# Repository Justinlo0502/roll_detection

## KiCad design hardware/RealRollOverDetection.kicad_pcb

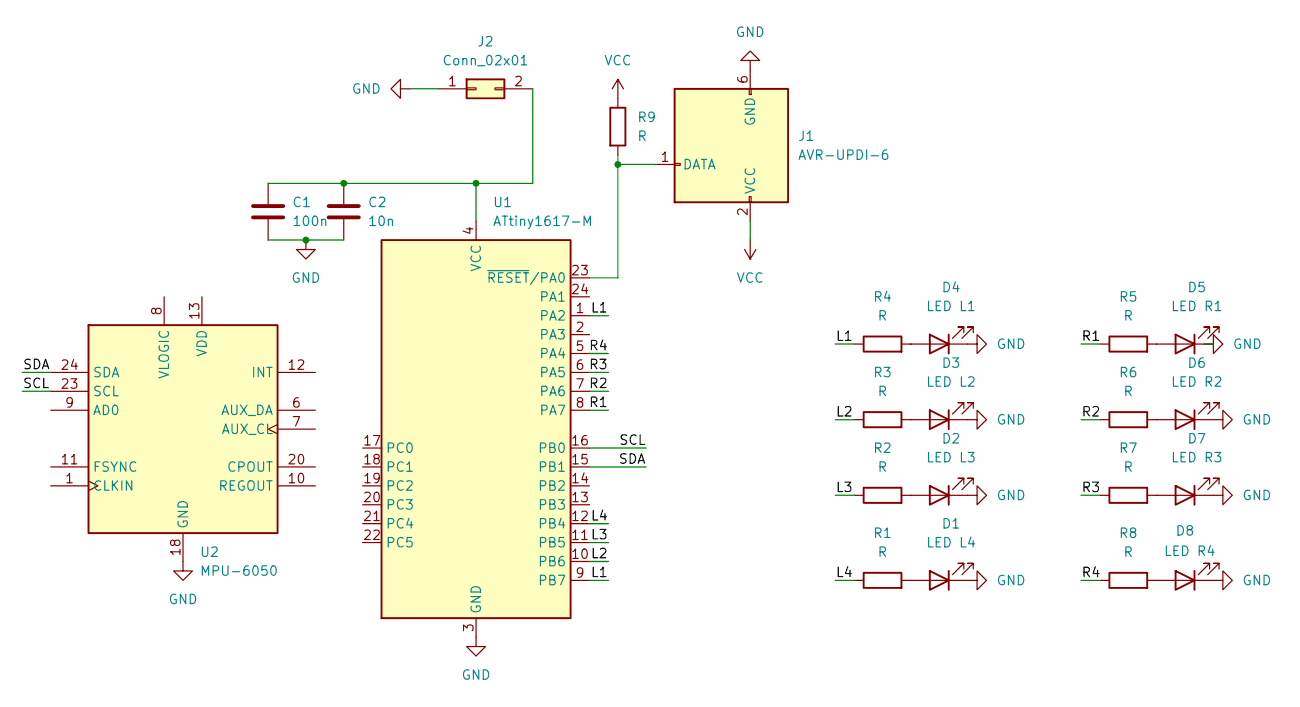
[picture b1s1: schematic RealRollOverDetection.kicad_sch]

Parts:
C1: 100n; C_0603_1608Metric
C2: 10n; C_0603_1608Metric
D1: LED L4; LED_0603_1608Metric
D2: LED L3; LED_0603_1608Metric
D3: LED L2; LED_0603_1608Metric
D4: LED L1; LED_0603_1608Metric
D5: LED R1; LED_0603_1608Metric
D6: LED R2; LED_0603_1608Metric
D7: LED R3; LED_0603_1608Metric
D8: LED R4; LED_0603_1608Metric
J1: AVR-UPDI-6; PinHeader_2x03_P2.54mm_Vertical_SMD
J2: Conn_02x01; PinHeader_1x02_P2.54mm_Vertical
R1, R2, R3, R4, R5, R6, R7, R8, R9: R; R_0603_1608Metric
U1: ATtiny1617-M; QFN-24-1EP_4x4mm_P0.5mm_EP2.6x2.6mm
U2: MPU-6050; InvenSense_QFN-24_4x4mm_P0.5mm

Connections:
/L1: R4.1, U1.1 (PA2), U1.9 (PB7)
/L2: R3.1, U1.10 (PB6)
/L3: R2.1, U1.11 (PB5)
/L4: R1.1, U1.12 (PB4)
/R1: R5.1, U1.8 (PA7)
/R2: R6.1, U1.7 (PA6)
/R3: R7.1, U1.6 (PA5)
/R4: R8.1, U1.5 (PA4)
/SCL: U1.16 (PB0), U2.23 (SCL)
/SDA: U1.15 (PB1), U2.24 (SDA)
GND: C1.2, C2.2, D1.1 (K), D2.1 (K), D3.1 (K), D4.1 (K), D5.1 (K), D6.1 (K), D7.1 (K), D8.1 (K), J1.6 (GND), J2.1, U1.3 (GND), U1.25 (GND), U2.18 (GND)
unnamed: D1.2 (A), R1.2
unnamed: D2.2 (A), R2.2
unnamed: D3.2 (A), R3.2
unnamed: D4.2 (A), R4.2
unnamed: D5.2 (A), R5.2
unnamed: D6.2 (A), R6.2
unnamed: D7.2 (A), R7.2
unnamed: D8.2 (A), R8.2
unnamed: J1.1 (DATA), R9.2, U1.23 (~RESET/PA0)
unnamed: C1.1, C2.1, J2.2, U1.4 (VCC)
VCC: J1.2 (VCC), R9.1

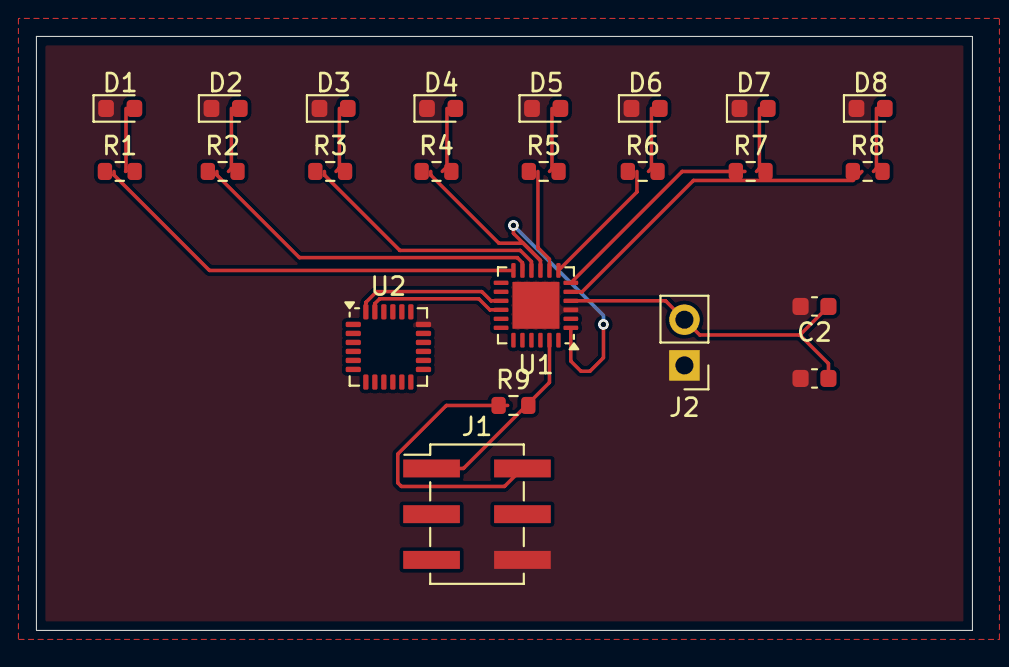
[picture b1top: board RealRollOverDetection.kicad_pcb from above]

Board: 2 copper layers, 52.0 x 33.0 mm, 23 parts (0 on the bottom side), 22 nets.

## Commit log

2024-02-28 initialize project
2024-02-28 Added test code
2024-09-09 Upload all the correct documents
2024-09-10 Updated with comments
